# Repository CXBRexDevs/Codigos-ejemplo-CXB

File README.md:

# CXB Rex

Es una plataforma de desarrollo orientada hacia control avanzado de variables físicas, que integra drivers de motores, interfaces de comunicación y acoplo de sensores,  con el fin de facilitar experimentos para el desarrollo academico superior. En la siguiente [imagen](https://github.com/CXBRexDevs/Codigos-ejemplo-CXB/blob/015453cbffbb8909efc1b8809f53027d9adc56b4/images/BASEDibujoCXBareas.png) se aprecia la disposición de los periféricos disponibles al usuario. Mientras qeu las conexiones internas de la PCB se documentan en los [planos]() del proyecto.

En este repositorio se encuentran los planos y archivos de fabricación, códigos ejemplo, circuitos de prueba externos a la tarjeta electronica y entre otros archivos de interés.

# Guía de instalación programador

## *Advertencia: Pickit 3 solo es compatible con versiones de MPLAB anteriores a la versión 6.05*

## Programas necesarios

- MPLAB IDE

- Compilador XC32

- MPLAB Code Configurator
  
  ## MPLAB IDE
  
  Para la instalación de estos dos programas se debe ingresar a [MPLAB® X IDE | Microchip Technology](https://www.microchip.com/en-us/tools-resources/develop/mplab-x-ide) . Una vez en la página, seleccione la opción “Download MPLAB X IDE” y posteriormente descargue la versión de Windows.

Puede descargar versiones anteriores navegando en la misma página al botón "Go To Downloads Archives" y buscando en el navegador su versión predilecta.

Una vez descargado el archivo abra el ejecutable.

Ahora debe dar clic en aceptar el acuerdo de usuario y así poder seguir el proceso de instalación haciendo clic en ‘next’.

https://github.com/CXBRexDevs/Codigos-ejemplo-CXB/blob/main/images/2023-07-07-10-25-39-image.png?raw=true)

Escoja el directorio donde desea instalar MPLAB X IDE y pulse siguiente.

Ahora el instalador preguntará cuáles programas desea instalar, se recomienda la instalación de todos los aplicativos de la imagen abajo, pero para el uso de CXB-REX, solo es necesario “MPLAB X IDE” y “32 bit MCUs”.

Al hacer clic en siguiente se iniciará la instalación.

Espere a que termine la instalación y haga clic en finalizar una vez la opción se habilite.

## MPLAB XC32 COMPILER:

Ingrese a [MPLAB XC Compiler Downloads and Documentation | Microchip Technology](https://www.microchip.com/en-us/tools-resources/develop/mplab-xc-compilers/downloads-documentation) y seleccione la opción “XC32 Compilers” y posteriormente descargue la versión de Windows.

Una vez se ha descargado el instalador, ejecute la aplicación, los pasos a seguir son los mismos que para la instalación de MPLAB IDE, excepto por el tipo de licencia, en la cual debe seleccionar ‘free’.

Después de escoger la licencia, se escoge el directorio de instalación y el programa procederá a instalarse, de la misma manera que MPLAB IDE, solo que al final dirá la información de la licencia, pero debido a que se seleccionó gratuita solo se debe dar clic en next para finalizar.

## MPLAB Harmony V3

El primer paso es abrir MPLAB IDE, luego seleccionar el apartado de "tools" en la parte superior de la pantalla, y en la ventana desplegada seleccionar "Plugins".

En la ventana de plugins seleccionar la pestaña de "Updates" y en el listado buscar si se encuentra “MPLAB@ Code Configurator”, si es el caso seleccionelo y haga clic en "Update".

Aparecerá una nueva ventana dandole la bienvenida al instalador, haga clic en “Next” empezará la instalación.

Luego de terminar aparecerá una ventana solicitando reiniciar MPLAB IDE para que los cambios tengan efecto, acepte y finalice.

## Extensiones de Harmony 3:

Una vez se ha reiniciado MPLAB IDE con la instalación de harmony 3, seleccionamos en la pestaña Tools -> Embedded -> MPLAB Code Configurator v5 Open/Close

La primera vez que se inicia el programa mostrará un cuadro con el framework a elegir, en este caso se selecciona Harmony.

Una vez seleccionado aparecerá una tabla que indicara las extensiones requeridas.

En caso de ser necesario también puede seleccionar las casillas del contenido opcional para que sean también se instale ese contenido, haga clic en "Finish" y espere, esto puede tomar unos minutos.  Se abrirá el siguiente entorno cuando haya terminado

Ahora puede seguir la guía en "Mi primer proyecto", la cuál le guirá en este mismo proceso y le indicará como programar comunicación UART a USB o UART a RS232. También puede descargar este repositorio y abrir algún otro de los proyectos aquí descritos.

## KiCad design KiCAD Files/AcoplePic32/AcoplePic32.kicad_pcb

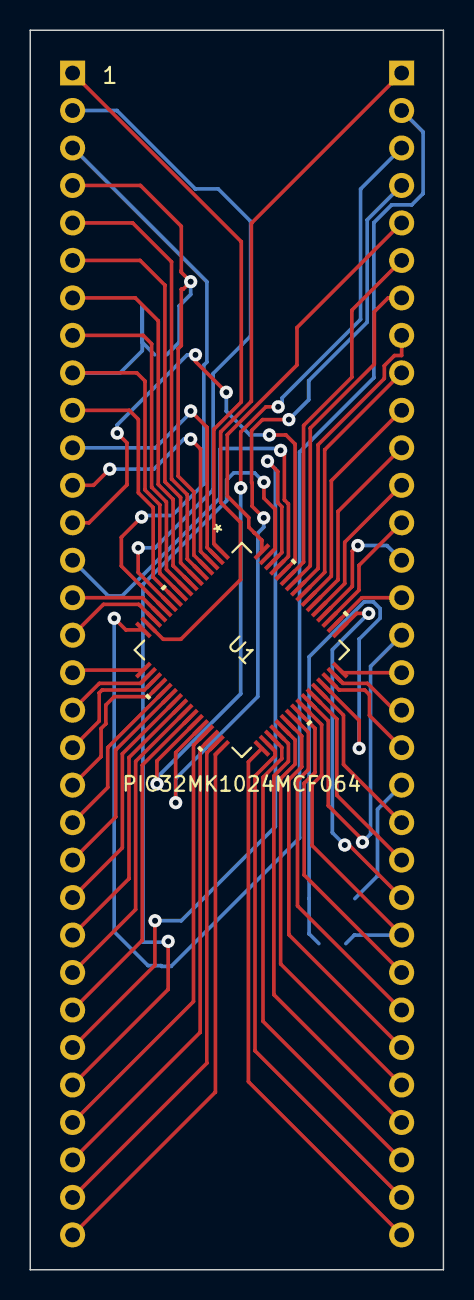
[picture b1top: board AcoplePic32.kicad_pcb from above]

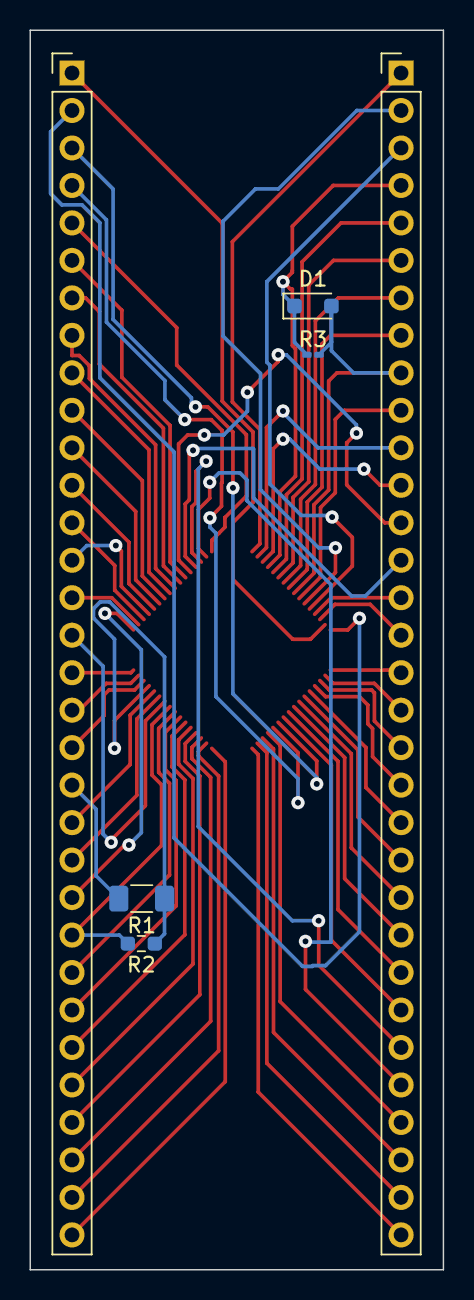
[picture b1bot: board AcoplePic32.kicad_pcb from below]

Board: 2 copper layers, 28.0 x 84.0 mm, 7 parts (6 on the bottom side), 65 nets.

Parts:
D1: ZENER 3.3v; D_SOD-323_HandSoldering
J1, J3: Conn_01x32; PinHeader_1x32_P2.54mm_Vertical
R1: 470; R_1206_3216Metric_Pad1.30x1.75mm_HandSolder
R2: 2200; R_0603_1608Metric_Pad0.98x0.95mm_HandSolder
R3: 100; R_0201_0603Metric_Pad0.64x0.40mm_HandSolder
U1: PIC32MK1024MCF064; TQFP64_PT_MCH

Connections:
An17: D1.1 (A1), J1.4, R3.1, U1.4 (AN19/CVD19/RPG6/PMA5/RG6)
MuEnable1H: J1.2, U1.11 (AN10/CVD10/RPA12/RA12)
MuEnable1L: J1.3, U1.12 (AN9/CVD9/RPA11/USBOEN1/RA11)
MuEnable2H: J3.64 (Pin_1), U1.15 (PGD3/VREF-/OA2IN-/AN2/C2IN1-/RPB0/CTED2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)
MuEnable2L: J3.63 (Pin_2), U1.16 (PGC3/OA1OUT/VREF+/AN3/C1IN4-/C4IN2-/RPB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)
MuEnable3H: J3.62 (Pin_3), U1.27 (AN12/CVD12/C2IN2-/C5IN2-/FLT5/PMA11/RE12)
MuEnable3L: J3.61 (Pin_4), U1.28 (AN13/CVD13/C3IN2-/FLT6/PMA10/RE13)
MuPWM1H: J1.11, U1.2 (RPB14/PWM1H/VBUSON1/PMD6/RB14)
MuPWM1L: J1.12, U1.3 (RPB15/PWM7H/PWM1L/PMD7/RB15)
MuPWM2H: J1.27, U1.62 (RPB12/PWM2H/PMD2/RB12)
MuPWM2L: J1.28, U1.63 (RPB13/PWM8H/PWM2L/CTPLS/PMD3/RB13)
MuPWM3H: J1.13, U1.60 (RPB10/PWM3H/PMD0/RB10)
MuPWM3L: J1.14, U1.61 (RPB11/PWM9H/PWM3L/PMD1/RB11)
MuRS232RX: R1.1, R2.1, U1.45 (DAC2/AN48/CVD48/RPC10/PMA14/PMCS/RC10)
unnamed: J1.1, U1.1 (TCK/RPA7/PWM10H/PWM4L/PMD5/RA7)
unnamed: J1.5, U1.5 (AN18/CVD18/RPG7/PMA4/RG7)
unnamed: J1.6, U1.6 (AN17/CVD17/RPG8/PMA3/RG8)
unnamed: J1.7, U1.7 (MCLR)
unnamed: J1.8, U1.8 (AN16/CVD16/RPG9/PMA2/RG9)
unnamed: J1.10, U1.10 (VDD)
unnamed: J1.17, U1.17 (PGC1/OA1IN+/AN4/C1IN1+/C1IN3-/C2IN3-/RP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)
unnamed: J1.18, U1.18 (PGD1/OA1IN-/AN5/CTCMP/C1IN1-/RTCC/RPB3/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)
unnamed: J1.19, U1.19 (AVDD)
unnamed: J1.20, U1.20 (AVSS)
unnamed: J1.21, U1.21 (OA3OUT/AN6/CVD6/C3IN4-/C4IN1+/C4IN4-/RP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)
unnamed: J1.22, U1.22 (OA3IN-/AN7/CVD7/C3IN1-/C4IN1-/RPC1/PMA7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)
unnamed: J1.23, U1.23 (OA3IN+/AN8/CVD8/C3IN1+/C3IN3-/RPC2/FLT3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)
unnamed: J1.24, U1.24 (AN11/CVD11/C1IN2-/FLT4/PMA12/RC11)
unnamed: J1.25, U1.25 (VSS)
unnamed: J1.26, U1.26 (VDD)
unnamed: J1.31, U1.31 (TDI/DAC3/AN26/CVD26/RPA8/PMA9/RA8)
unnamed: J1.32, U1.32 (FLT15/RPB4/PMA8/RB4)
unnamed: J3.60 (Pin_5), U1.64 (TDO/PWM4H/PMD4/RA10)
unnamed: J3.59 (Pin_6), U1.59 (RPF1/PWM11L/RF1)
unnamed: J3.58 (Pin_7), U1.58 (RPF0/PWM11H/RF0)
unnamed: J3.57 (Pin_8), U1.57 (VDD)
unnamed: J3.56 (Pin_9), U1.56 (VSS)
unnamed: J3.55 (Pin_10), U1.55 (RPC9/PWM11H/PWM5L/RC9)
unnamed: J3.54 (Pin_11), U1.54 (TRD3/RPD6/PWM12L/RD6)
unnamed: J3.53 (Pin_12), U1.53 (TRD2/RPD5/PWM12H/PMRD/RD5)
unnamed: J3.50 (Pin_15), U1.50 (TRCLK/RPC6/PWM6H/RC6)
unnamed: J3.49 (Pin_16), U1.42 (RD8)
unnamed: J3.48 (Pin_17), U1.48 (SOSCO/RPB8/RB8)
unnamed: J3.47 (Pin_18), U1.47 (SOSCI/RPC13/RC13)
unnamed: J3.46 (Pin_19), U1.46 (OA5OUT/AN25/CVD25/C5IN4-/RPB7/SCK1/INT0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)
unnamed: J3.40 (Pin_25), U1.40 (OSCO/CLKO/RPC15/RC15)
unnamed: J3.39 (Pin_26), U1.39 (OSCI/CLKI/AN49/CVD49/RPC12/RC12)
unnamed: J3.38 (Pin_27), U1.38 (VDD)
unnamed: J3.37 (Pin_28), U1.37 (D+)
unnamed: J3.36 (Pin_29), U1.36 (D-)
unnamed: J3.35 (Pin_30), U1.35 (VUSB3V3)
unnamed: J3.34 (Pin_31), U1.34 (VBUS)
unnamed: J3.33 (Pin_32), U1.33 (OA5IN+/DAC1/AN24/CVD24/C5IN1+/C5IN3-/RP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)
QEIA1: J3.52 (Pin_13), U1.51 (TRD0/RPC7/PWM12H/PWM6L/RC7)
QEIA2: J1.29, U1.29 (AN14/CVD14/RPE14/FLT7/PMA1/RE14)
QEIA3: J1.15, U1.13 (OA2OUT/AN0/C2IN4-/C4IN3-/RPA0/RA0)
QEIB1: J3.51 (Pin_14), U1.52 (TRD1/RPC8/PWM5H/PMWR/RC8)
QEIB2: J1.30, U1.30 (AN15/CVD15/RPE15/FLT8/PMA0/RE15)
QEIB3: J1.16, U1.14 (OA2IN+/AN1/C2IN1+/RPA1/RA1)
RS232RX: J3.45 (Pin_20), R1.2
RS232TX: J3.43 (Pin_22), U1.43 (PGD2/RPB5/USBID1/RB5)
UART_RX: J3.44 (Pin_21), U1.44 (PGC2/RPB6/SCK2/PMA15/RB6)
UART_TX: J3.42 (Pin_23), U1.49 (TMS/OA5IN-/AN27/CVD27/C5IN1-/RPB9/RB9)
VSS: J3.41 (Pin_24), R2.2, U1.41 (VSS)
VSS9: D1.2 (A2), J1.9, R3.2, U1.9 (VSS)

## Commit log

2023-07-05 Create Manual.md
    Manual que describe la creación de un proyecto básico, incluyendo encendido y apagado de LEDS, detección de pulsado de un botón y comunicación serial.
2023-07-07 Rename Manual.md to README.md
